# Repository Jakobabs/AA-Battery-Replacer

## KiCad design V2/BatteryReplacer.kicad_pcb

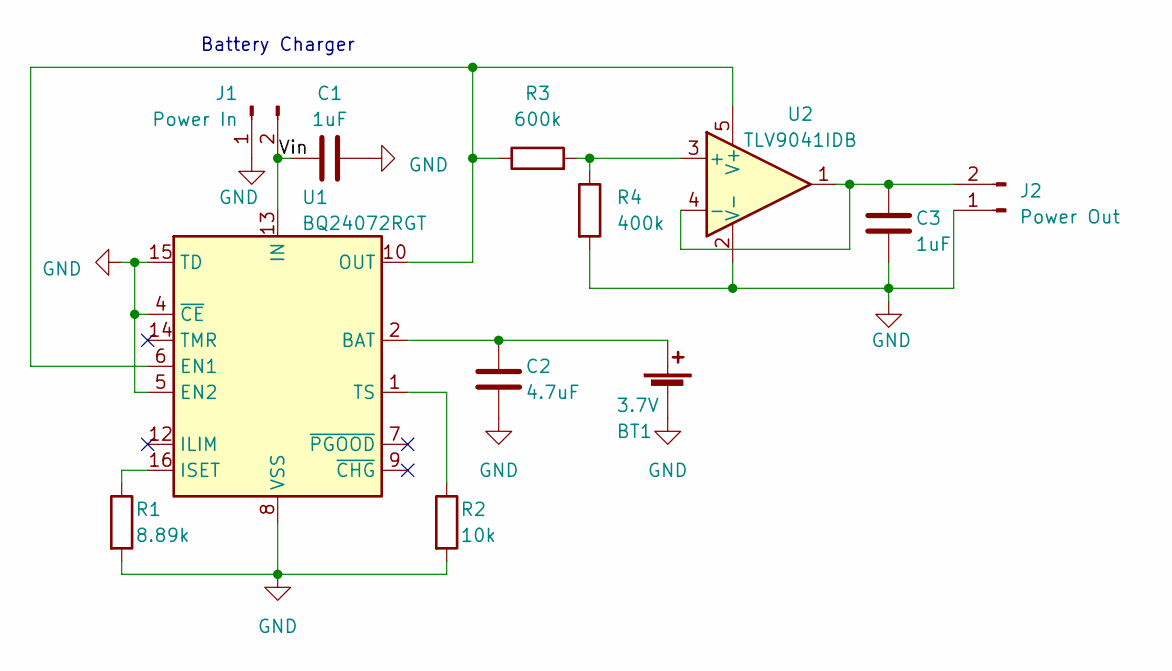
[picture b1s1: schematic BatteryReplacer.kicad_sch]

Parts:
BT1: 3.7V; PinHeader_1x02_P2.54mm_Vertical
C1, C3: 1uF; C_0402_1005Metric_Pad0.74x0.62mm_HandSolder
C2: 4.7uF; C_0402_1005Metric_Pad0.74x0.62mm_HandSolder
J1: Power In; PinHeader_1x02_P2.54mm_Vertical
J2: Power Out; PinHeader_1x02_P2.54mm_Vertical
R1: 8.89k; R_0402_1005Metric_Pad0.72x0.64mm_HandSolder
R2: 10k; R_0402_1005Metric_Pad0.72x0.64mm_HandSolder
R3: 600k; R_0402_1005Metric_Pad0.72x0.64mm_HandSolder
R4: 400k; R_0402_1005Metric_Pad0.72x0.64mm_HandSolder
U1: BQ24072RGT; VQFN-16-1EP_3x3mm_P0.5mm_EP1.68x1.68mm
U2: TLV9041IDB; SOT-23-5

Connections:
/Vin: C1.1, J1.2, U1.13 (IN)
GND: BT1.2 (-), C1.2, C2.2, C3.1, J1.1, J2.1, R1.2, R2.2, R4.2, U1.4 (~CE), U1.5 (EN2), U1.8 (VSS), U1.15 (TD), U1.17 (VSS), U2.2 (V-)
unnamed: BT1.1 (+), C2.1, U1.2 (BAT), U1.3 (BAT)
unnamed: C3.2, J2.2, U2.1, U2.4 (-)
unnamed: R3.1, U1.6 (EN1), U1.10 (OUT), U1.11 (OUT), U2.5 (V+)
unnamed: R1.1, U1.16 (ISET)
unnamed: R2.1, U1.1 (TS)
unnamed: R3.2, R4.1, U2.3 (+)

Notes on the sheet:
Battery Charger

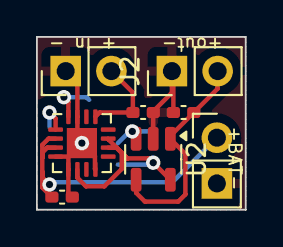
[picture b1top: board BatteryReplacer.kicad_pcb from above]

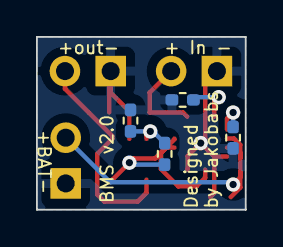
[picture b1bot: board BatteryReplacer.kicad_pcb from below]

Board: 2 copper layers, 11.6 x 9.6 mm, 12 parts (4 on the bottom side), 8 nets.
